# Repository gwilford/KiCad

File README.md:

View this project on [CADLAB.io](https://cadlab.io/project/25430). 

# KiCad
 Schematics and PCB design

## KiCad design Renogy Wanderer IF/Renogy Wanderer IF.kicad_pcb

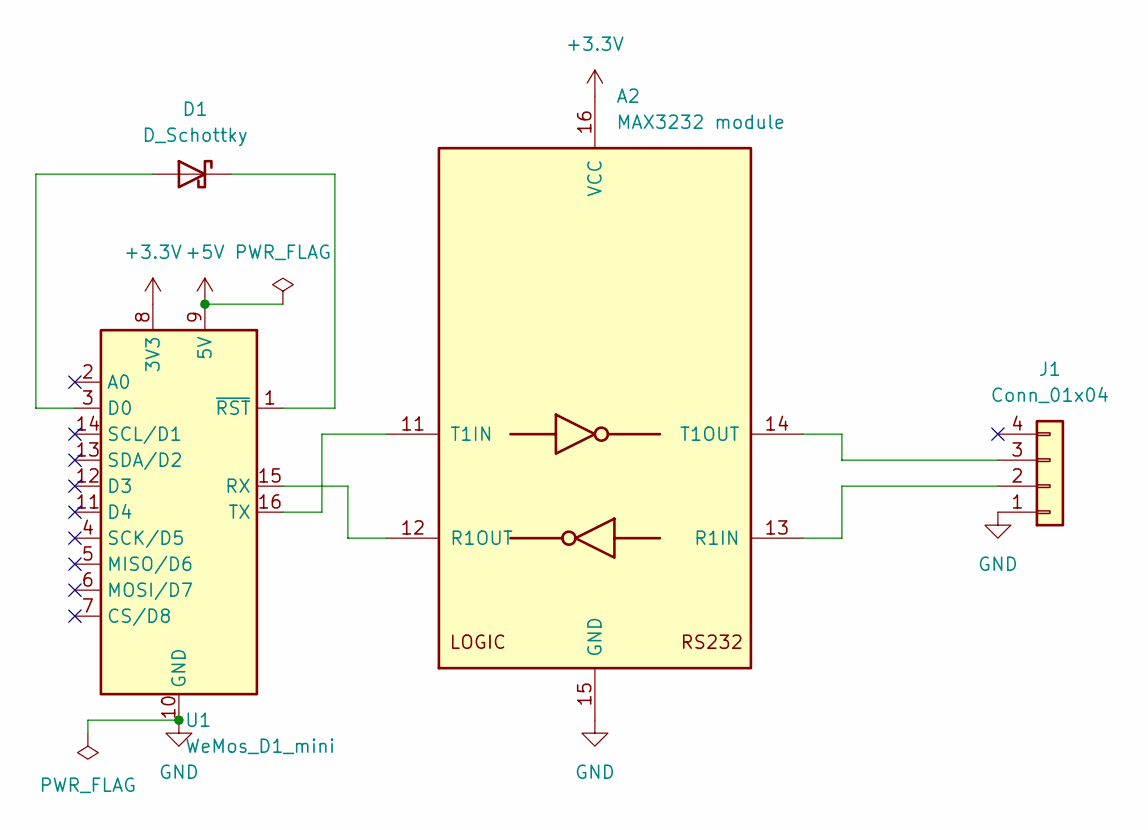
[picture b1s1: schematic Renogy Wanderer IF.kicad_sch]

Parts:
A2: MAX3232 module
D1: D_Schottky
J1: Conn_01x04; SolderWire-0.1sqmm_1x04_P3.6mm_D0.4mm_OD1mm
U1: WeMos_D1_mini; WEMOS_D1_mini_light

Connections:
+3V3: A2.16 (VCC), U1.8 (3V3)
+5V: U1.9 (5V)
GND: A2.15 (GND), J1.1, U1.10 (GND)
unnamed: A2.11 (T1IN), U1.16 (TX)
unnamed: A2.12 (R1OUT), U1.15 (RX)
unnamed: A2.13 (R1IN), J1.2
unnamed: A2.14 (T1OUT), J1.3
unnamed: D1.1 (K), U1.1 (~RST)
unnamed: D1.2 (A), U1.3 (D0)

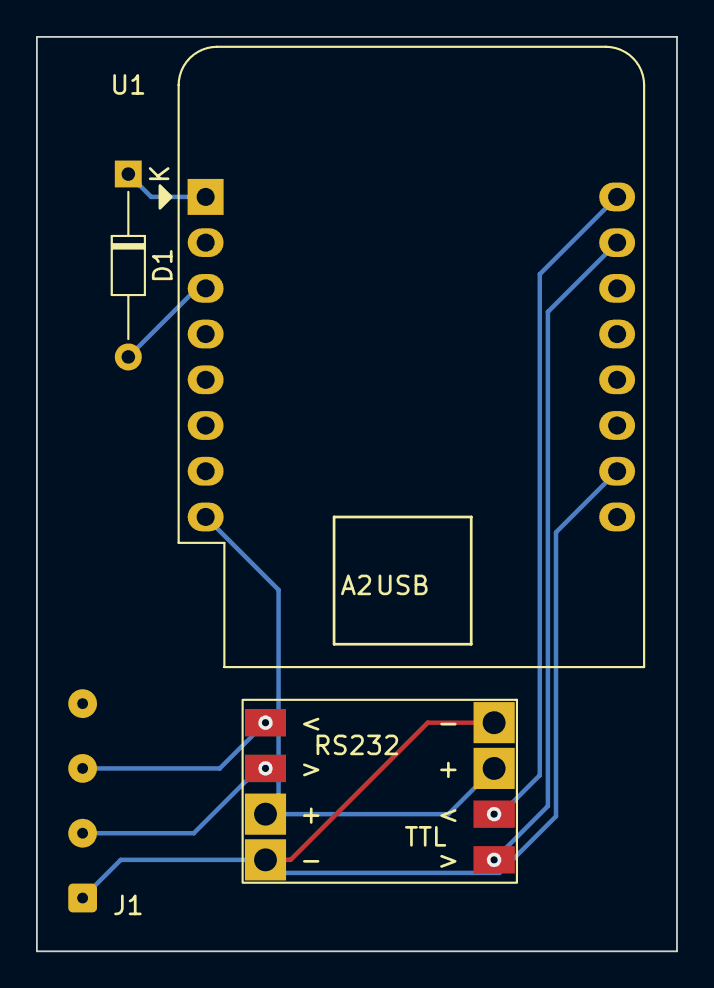
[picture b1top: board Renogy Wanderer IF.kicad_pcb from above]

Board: 2 copper layers, 35.6 x 50.8 mm, 4 parts (0 on the bottom side), 8 nets.

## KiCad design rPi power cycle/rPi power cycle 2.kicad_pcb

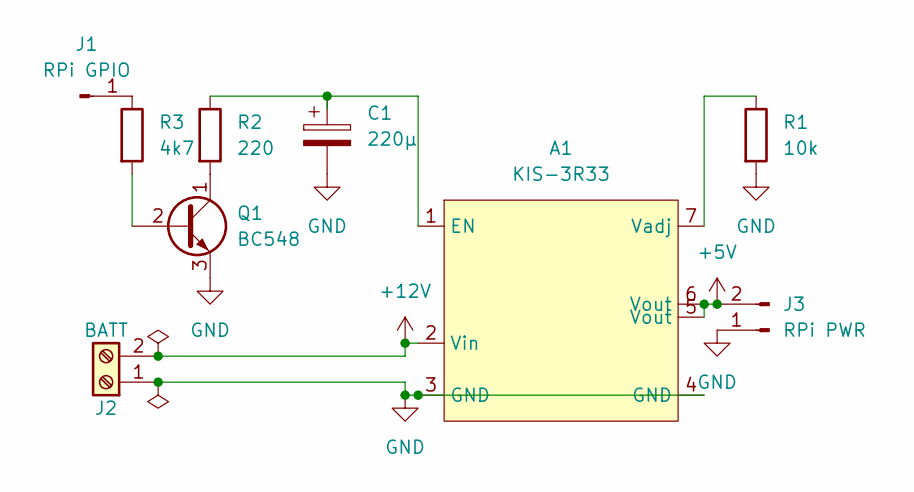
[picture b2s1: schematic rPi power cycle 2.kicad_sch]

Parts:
A1: KIS-3R33; KIS-3R33S package
C1: 220µ; CP_Radial_D8.0mm_P5.00mm
J1: RPi GPIO; PinHeader_1x01_P2.54mm_Vertical
J2: BATT; TerminalBlock_bornier-2_P5.08mm
J3: RPi PWR; PinHeader_1x02_P2.54mm_Vertical
Q1: BC548; TO-92_Wide
R1: 10k; R_Axial_DIN0207_L6.3mm_D2.5mm_P2.54mm_Vertical
R2: 220; R_Axial_DIN0207_L6.3mm_D2.5mm_P2.54mm_Vertical
R3: 4k7; R_Axial_DIN0207_L6.3mm_D2.5mm_P2.54mm_Vertical

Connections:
+5V: A1.5 (Vout), A1.6 (Vout), J3.2
+12V: A1.2 (Vin), J2.2
GND: A1.3 (GND), A1.4 (GND), C1.2, J2.1, J3.1, Q1.3 (E), R1.2
unnamed: A1.1 (EN), C1.1, R2.1
unnamed: A1.7 (Vadj), R1.1
unnamed: J1.1, R3.1
unnamed: Q1.1 (C), R2.2
unnamed: Q1.2 (B), R3.2

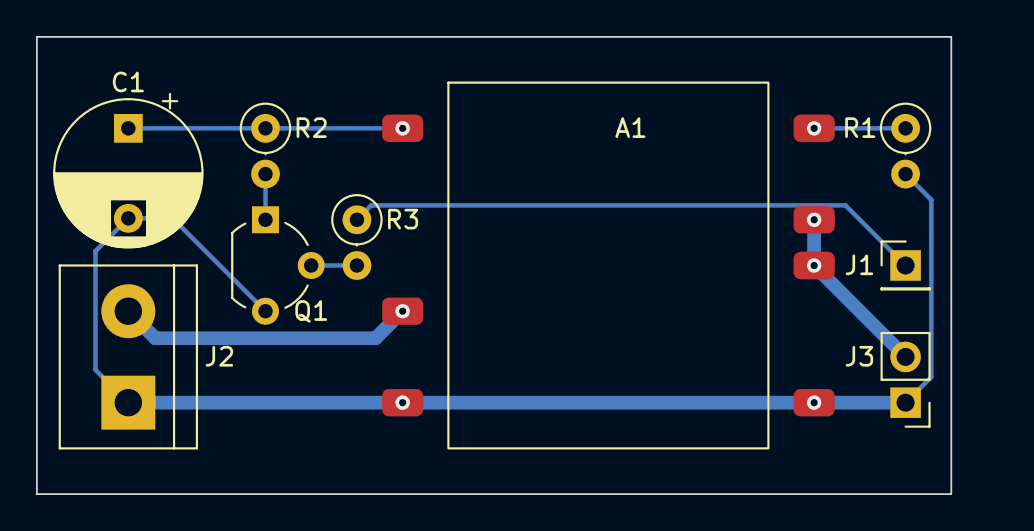
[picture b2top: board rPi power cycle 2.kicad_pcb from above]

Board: 2 copper layers, 53.3 x 25.4 mm, 9 parts (0 on the bottom side), 8 nets.

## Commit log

2022-04-13 Initial
2022-04-13 Swap Q1 and R3 locations
2022-04-13 Route tracks and cleanup
2022-04-13 Straighten some traces
    Shifted Q1 up a little
2022-04-13 Backlink to CADLAB.io has been added.
2022-04-13 Use via to simulate internal connections
2022-04-14 Move routing to back
    Simulate perfboard connections
2022-04-14 Add Power netclass and update track widths
2022-04-14 Move GPIO input pin
2022-04-14 Initial design
2022-04-14 Add MAX3232 module
2022-04-14 Footprints created
2022-04-14 Initial PCB design
2022-04-14 Add wake from sleep
2022-04-16 Invert the RS232 module for easier mounting
